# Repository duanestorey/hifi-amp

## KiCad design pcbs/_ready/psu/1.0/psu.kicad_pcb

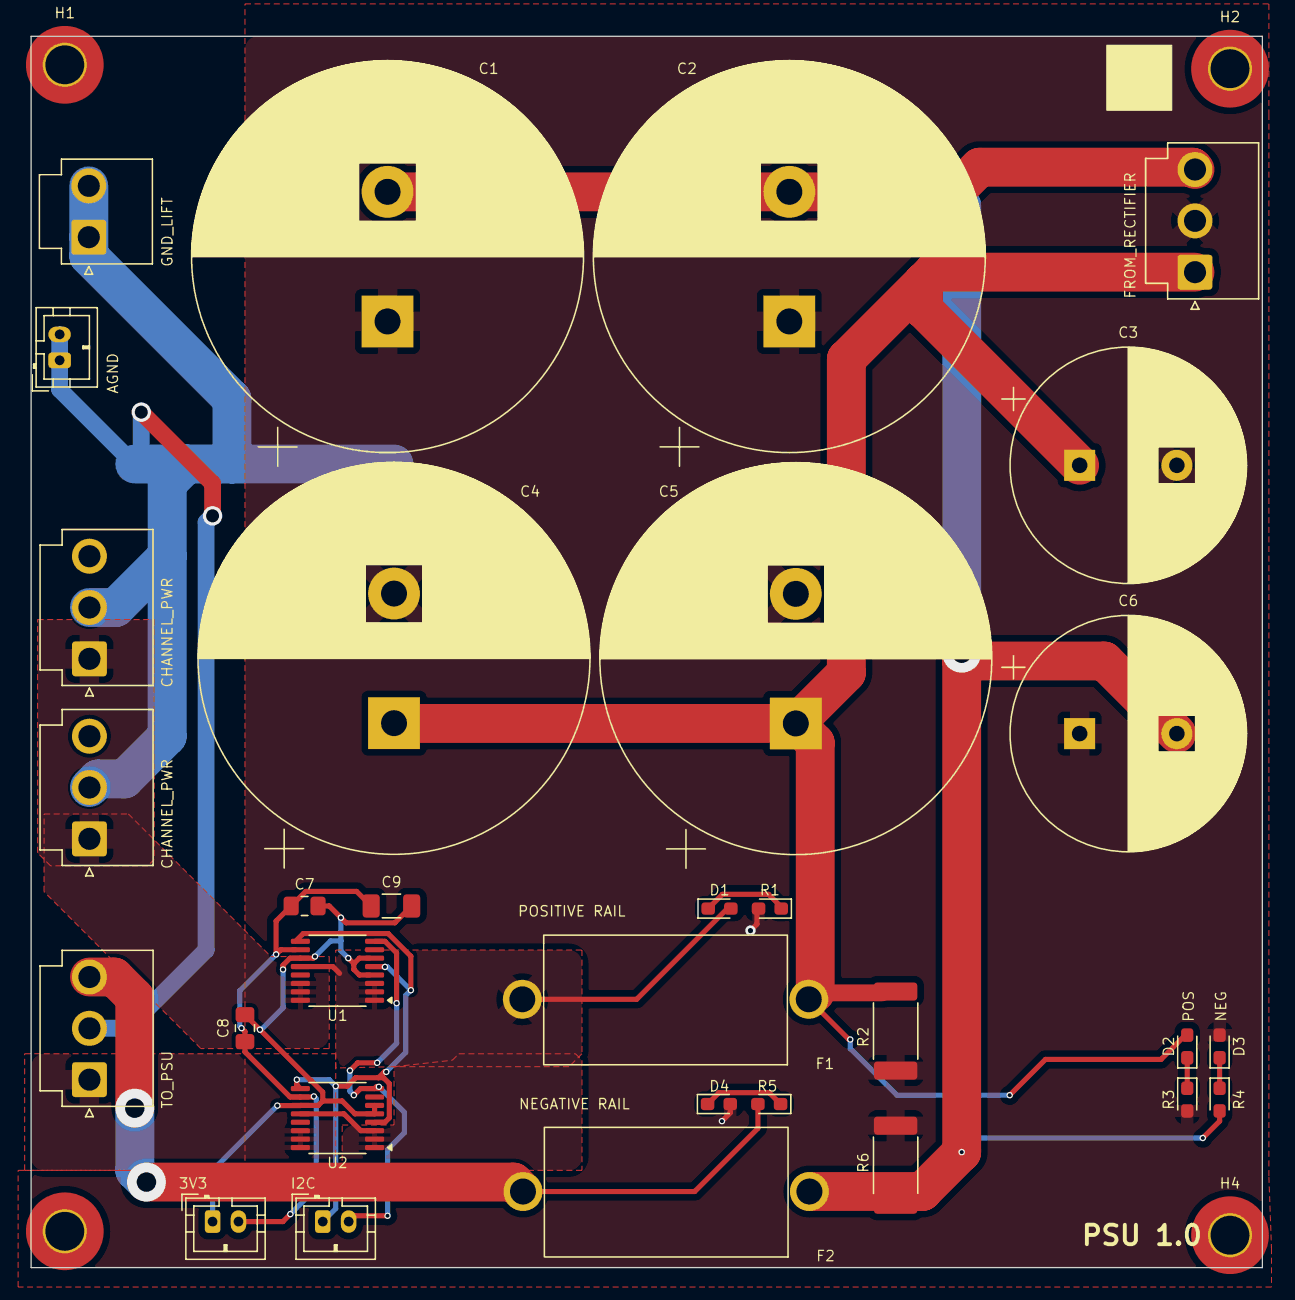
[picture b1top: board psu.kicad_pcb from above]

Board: 2 copper layers, 95.0 x 95.0 mm, 35 parts (0 on the bottom side), 15 nets.

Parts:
C1, C2, C4, C5: 15000U; CP_Radial_D30.0mm_P10.00mm_SnapIn
C3, C6: 3300u 50V; CP_Radial_D18.0mm_P7.50mm
C7, C8: 0.1u; C_0805_2012Metric_Pad1.18x1.45mm_HandSolder
C9: 10u; C_1206_3216Metric_Pad1.33x1.80mm_HandSolder
D1, D2: YELLOW; LED_0603_1608Metric_Pad1.05x0.95mm_HandSolder
D3, D4: BLUE; LED_0603_1608Metric_Pad1.05x0.95mm_HandSolder
F1, F2: Fuse_Small; Aliexpress Fuse 5x20
H1, H2, H3, H4: MountingHole; MountingHole_3mm_Pad_TopOnly
J1: Conn_01x02_Male; JST_VH_B2P-VH-B_1x02_P3.96mm_Vertical
J2, J4, J5, J6: Conn_01x03_Male; JST_VH_B3P-VH_1x03_P3.96mm_Vertical
J3, J7: Conn_01x02_Pin; JST_PH_B2B-PH-K_1x02_P2.00mm_Vertical
J8: Conn_01x02_Male; JST_PH_B2B-PH-K_1x02_P2.00mm_Vertical
R1, R3, R4, R5: 16K; LED_0603_1608Metric_Pad1.05x0.95mm_HandSolder
R2, R6: 1.5K 2W; R_2512_6332Metric_Pad1.40x3.35mm_HandSolder
U1, U2: INA260; TSSOP-16_4.4x5mm_P0.65mm

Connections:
3V3: C7.1, C8.1, C9.1, J7.2, U1.10 (VS), U2.10 (VS)
GND: C7.2, C8.2, C9.2, J7.1, U1.4 (A1), U1.6 (GND), U1.11 (GND), U2.5 (A0), U2.6 (GND), U2.11 (GND)
unnamed: D1.1 (K), R1.1
unnamed: D2.1 (K), R3.1
unnamed: D3.1 (K), R4.1
unnamed: D4.1 (K), R5.1
PGND: C1.1, C2.1, C3.2, C4.2, C5.2, C6.1, D3.2 (A), D4.2 (A), J1.1, J1.2, J2.2, J3.1, J3.2, J4.2, J5.2, J6.2, R1.2, R2.2, R3.2, R6.1
SCL: J8.1, U1.5 (A0), U1.9 (SCL), U2.4 (A1), U2.9 (SCL)
SDA: J8.2, U1.8 (SDA), U2.8 (SDA)
VM1: C1.2, C2.2, C6.2, F2.1, J2.3, R4.2, R6.2
VNOUT: F2.2, J4.3, J5.3, J6.3, R5.2
VP1: C3.1, C4.1, C5.1, D2.2 (A), F1.1, J2.1, R2.1
VPOUT: D1.2 (A), F1.2, U1.1 (IN+), U1.2 (IN+), U1.3 (IN+), U1.12 (VBUS), U2.1 (IN+), U2.2 (IN+), U2.3 (IN+), U2.12 (VBUS)
VPOUT_CHAN: J4.1, J5.1, U1.14 (IN-), U1.15 (IN-), U1.16 (IN-)
VPOUT_PSU: J6.1, U2.14 (IN-), U2.15 (IN-), U2.16 (IN-)

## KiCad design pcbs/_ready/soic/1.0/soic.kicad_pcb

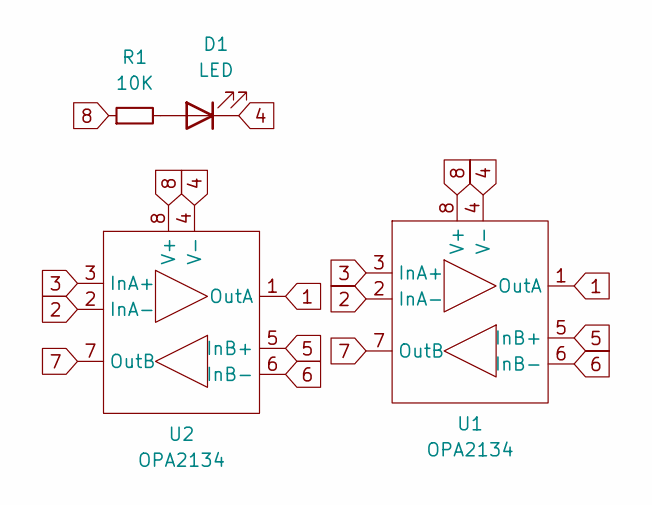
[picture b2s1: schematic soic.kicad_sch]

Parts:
D1: LED; LED_0603_1608Metric
R1: 10K; R_0603_1608Metric
U1: OPA2134; DIP-8_W7.62mm_Socket
U2: OPA2134; SOIC-8_3.9x4.9mm_P1.27mm

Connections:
1: U1.1 (OutA), U2.1 (OutA)
2: U1.2 (InA-), U2.2 (InA-)
3: U1.3 (InA+), U2.3 (InA+)
4: D1.1 (K), U1.4 (V-), U2.4 (V-)
5: U1.5 (InB+), U2.5 (InB+)
6: U1.6 (InB-), U2.6 (InB-)
7: U1.7 (OutB), U2.7 (OutB)
8: R1.1, U1.8 (V+), U2.8 (V+)
unnamed: D1.2 (A), R1.2

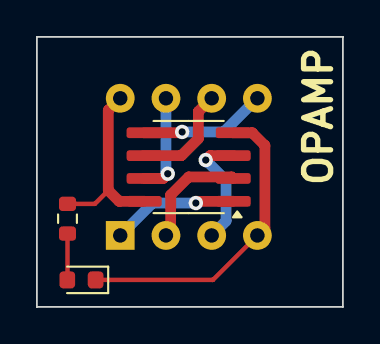
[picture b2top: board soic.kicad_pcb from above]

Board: 2 copper layers, 17.0 x 15.0 mm, 4 parts (0 on the bottom side), 9 nets.

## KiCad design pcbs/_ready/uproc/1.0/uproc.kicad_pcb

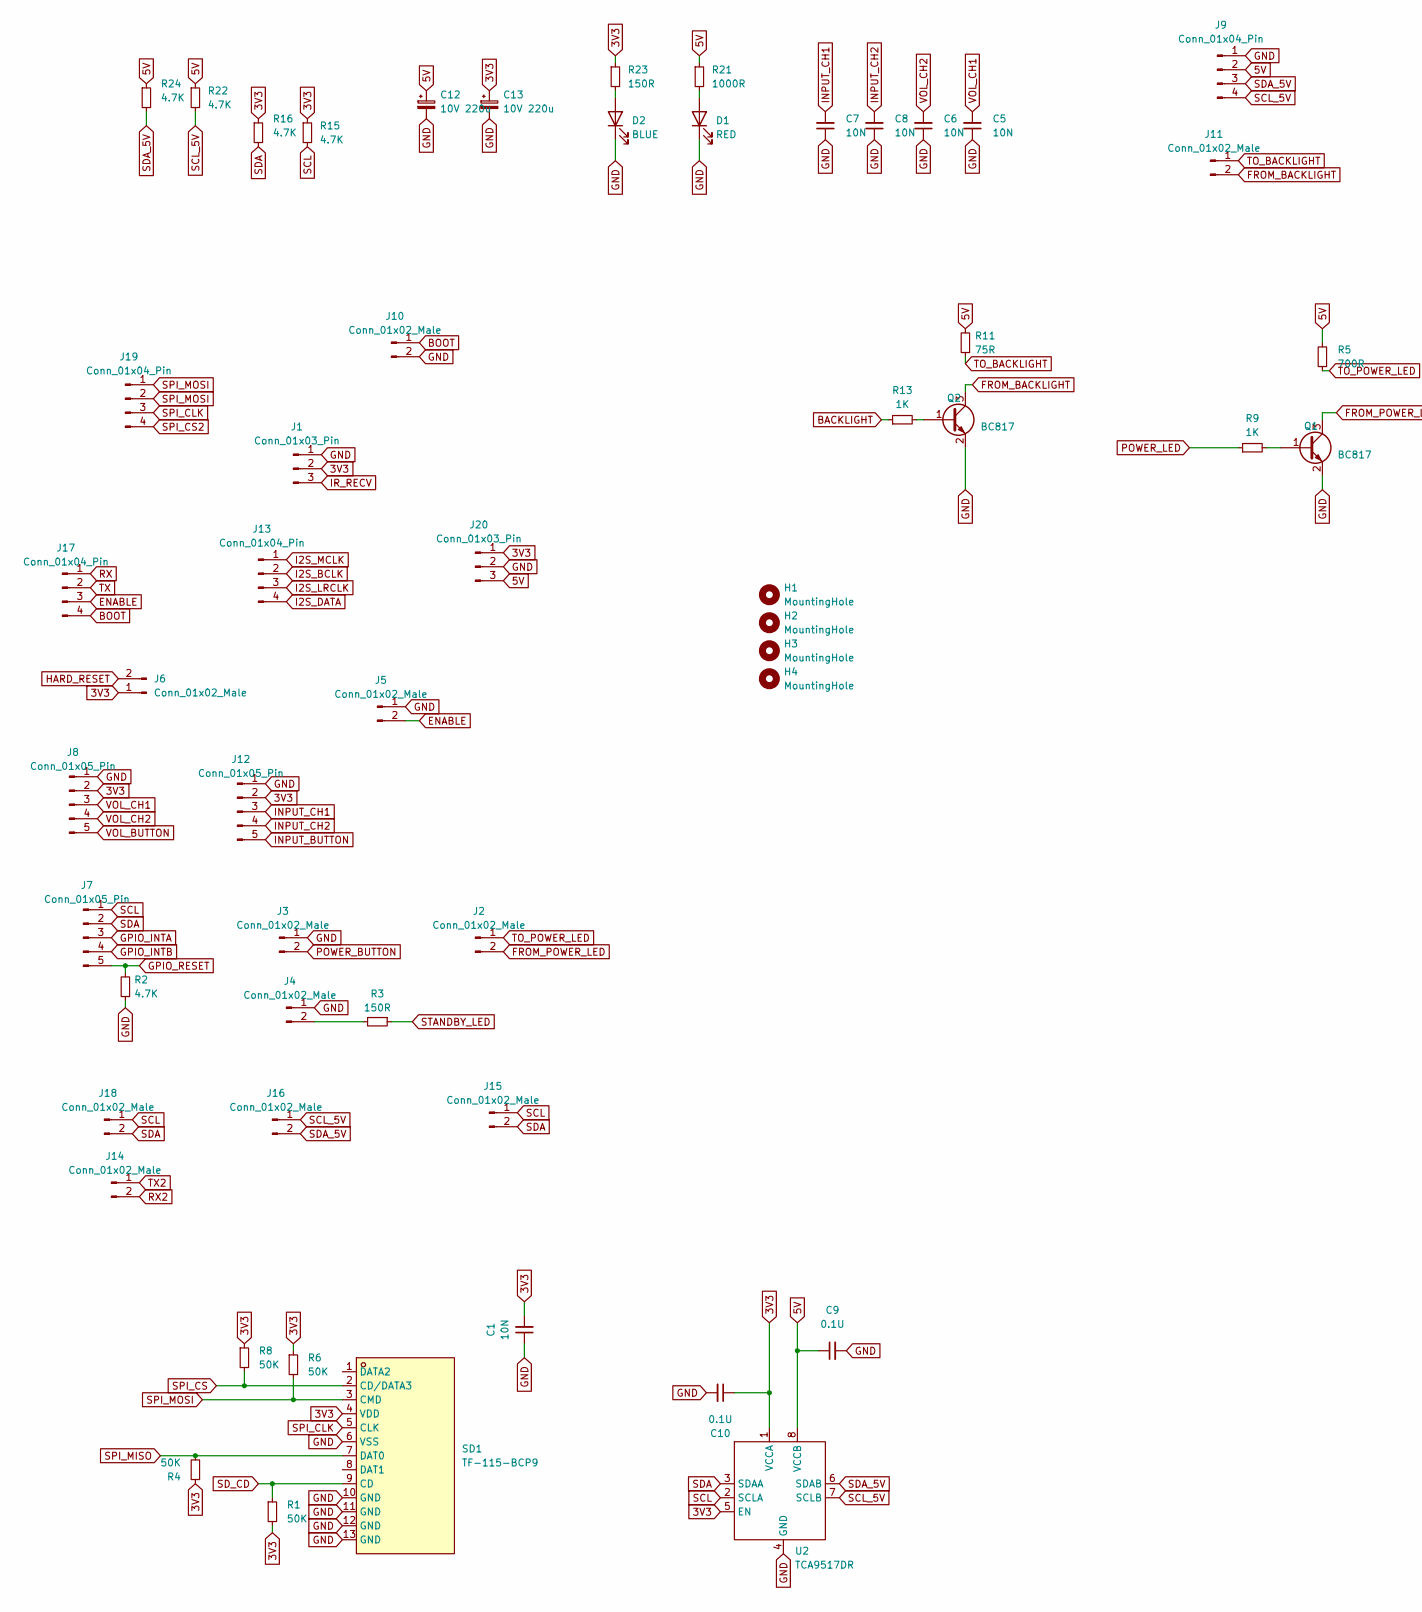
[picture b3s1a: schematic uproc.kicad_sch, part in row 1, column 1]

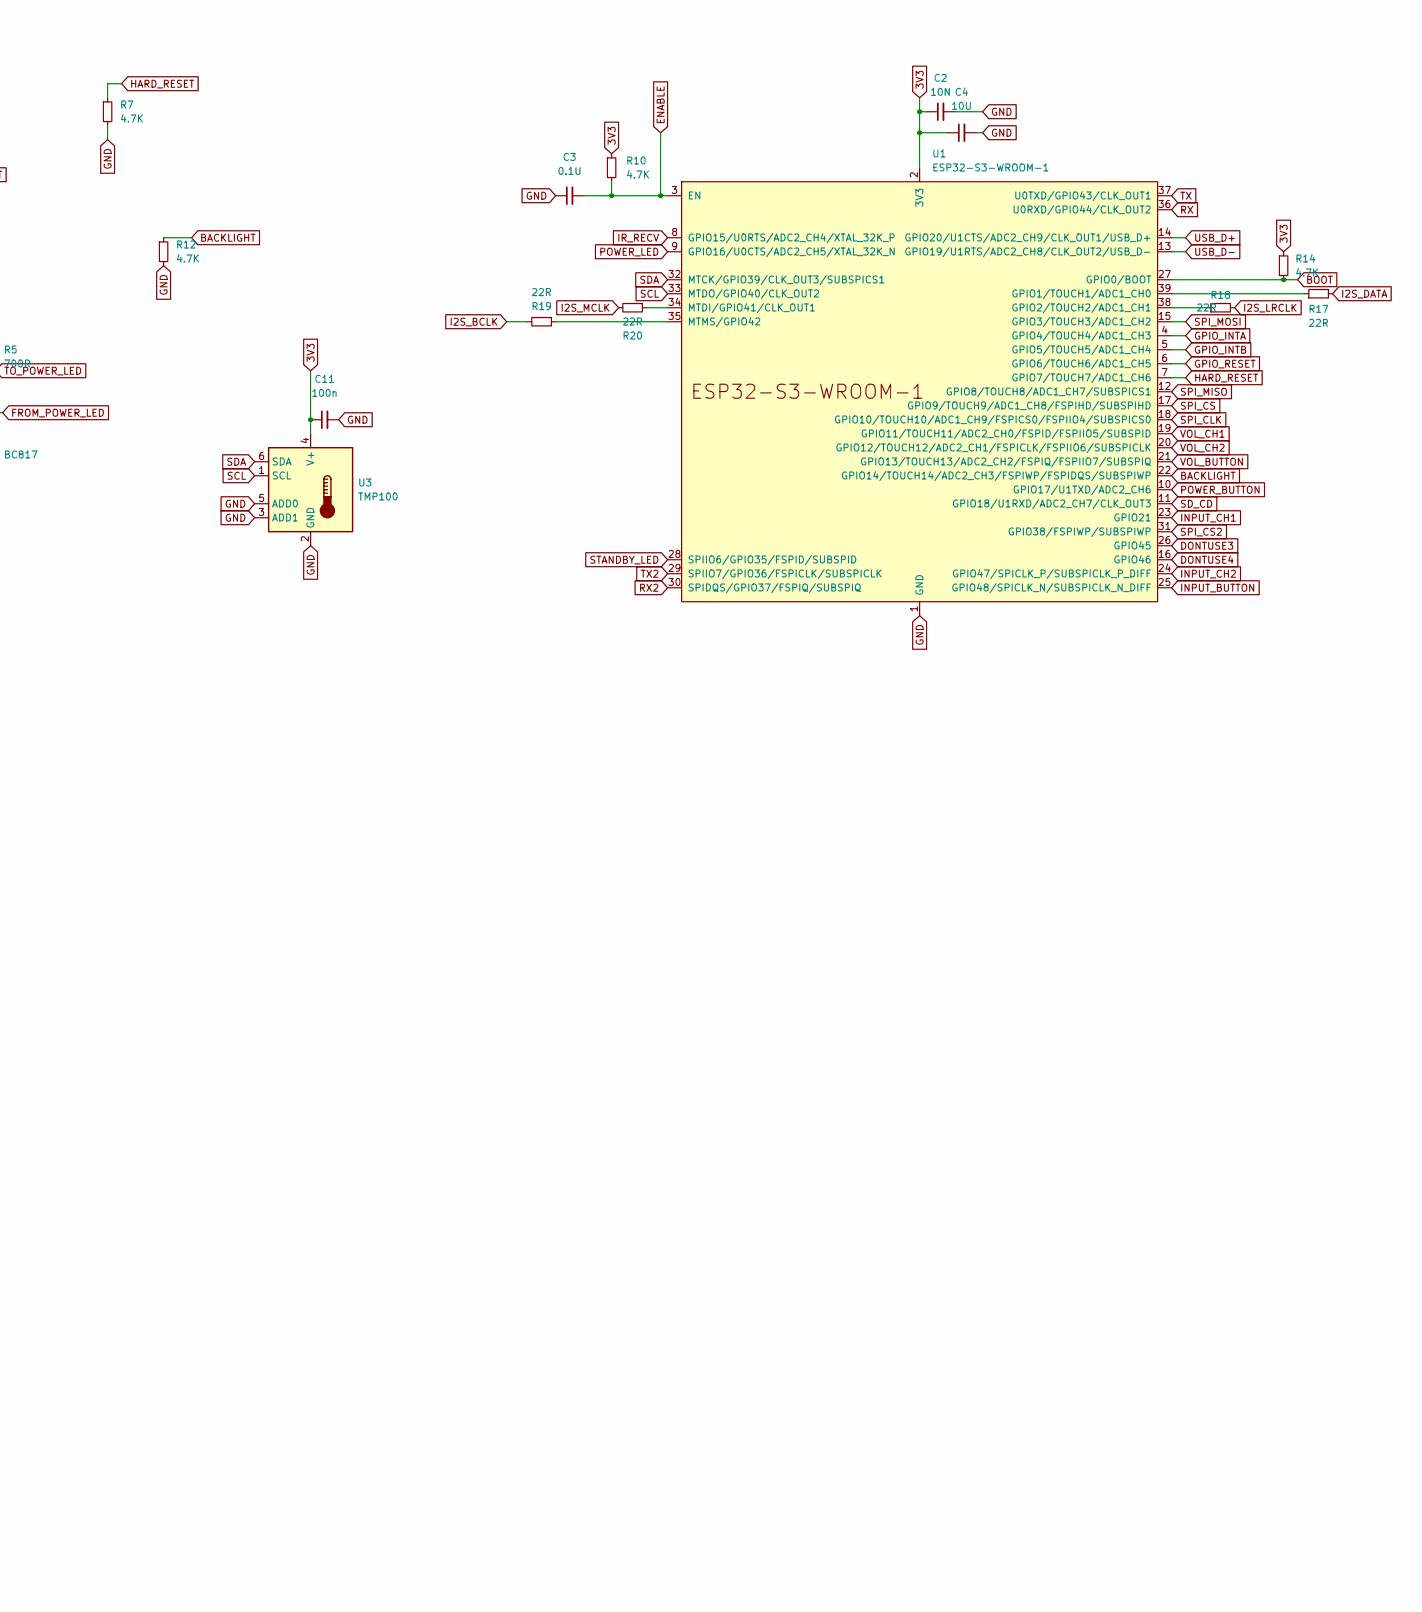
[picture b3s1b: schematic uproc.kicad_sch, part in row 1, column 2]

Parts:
C1, C2: 10N; C_0805_2012Metric_Pad1.18x1.45mm_HandSolder
C3, C9, C10: 0.1U; C_0805_2012Metric_Pad1.18x1.45mm_HandSolder
C4: 10U; C_1206_3216Metric_Pad1.33x1.80mm_HandSolder
C5, C6, C7, C8: 10N; C_0603_1608Metric_Pad1.08x0.95mm_HandSolder
C11: 100n; C_0805_2012Metric_Pad1.18x1.45mm_HandSolder
C12, C13: 10V 220u; CP_Radial_D6.3mm_P2.50mm
D1: RED; LED_0603_1608Metric; LCSC XL-1608UBC-04
D2: BLUE; LED_0603_1608Metric; LCSC NCD0603R1
H1, H2, H3, H4: MountingHole; MountingHole_3.2mm_M3_DIN965_Pad_TopOnly
J1, J20: Conn_01x03_Pin; JST_PH_B3B-PH-K_1x03_P2.00mm_Vertical
J2, J3, J4, J5, J11, J14, J15, J16, J18: Conn_01x02_Male; JST_PH_B2B-PH-K_1x02_P2.00mm_Vertical
J6, J10: Conn_01x02_Male; PinHeader_1x02_P2.54mm_Vertical
J7, J8, J12: Conn_01x05_Pin; JST_PH_B5B-PH-K_1x05_P2.00mm_Vertical
J9, J13, J17, J19: Conn_01x04_Pin; JST_PH_B4B-PH-K_1x04_P2.00mm_Vertical
Q1, Q2: BC817; TSOT-23; Mouser 637-BC817K-40
R1, R4, R6, R8: 50K; R_0603_1608Metric_Pad0.98x0.95mm_HandSolder
R2, R7, R10, R12, R14, R15, R16, R22, R24: 4.7K; R_0603_1608Metric_Pad0.98x0.95mm_HandSolder
R3, R23: 150R; R_0603_1608Metric_Pad0.98x0.95mm_HandSolder
R5: 700R; R_0603_1608Metric_Pad0.98x0.95mm_HandSolder
R9, R13: 1K; R_0603_1608Metric_Pad0.98x0.95mm_HandSolder
R11: 75R; R_0603_1608Metric_Pad0.98x0.95mm_HandSolder
R17, R18, R19, R20: 22R; R_0603_1608Metric; Mouser 603-RT0805FRE0722RL
R21: 1000R; R_0603_1608Metric_Pad0.98x0.95mm_HandSolder
SD1: TF-115-BCP9; TF-SMD_TF-115-BCP9; LCSC Part C720505
U1: ESP32-S3-WROOM-1
U2: TCA9517DR; SOIC-8_3.9x4.9mm_P1.27mm; Mouser 595-TCA9517DR
U3: TMP100; SOT-23-6

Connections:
3V3: C1.2, C2.1, C4.1, C10.1, C11.1, C13.1, J1.2, J6.1, J8.2, J12.2, J20.1, R1.2, R4.1, R6.1, R8.1, R10.1, R14.1, R15.1, R16.1, R23.1, SD1.4 (VDD), U1.2 (3V3), U2.1 (VCCA), U2.5 (EN), U3.4 (V+)
5V: C9.1, C12.1, J9.2, J20.3, R5.2, R11.2, R21.1, R22.1, R24.1, U2.8 (VCCB)
BACKLIGHT: R12.1, R13.1, U1.22 (GPIO14/TOUCH14/ADC2_CH3/FSPIWP/FSPIDQS/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)
BOOT: J10.1, J17.4, R14.2, U1.27 (GPIO0/BOOT)
DONTUSE3: U1.26 (GPIO45)
DONTUSE4: U1.16 (GPIO46)
ENABLE: C3.2, J5.2, J17.3, R10.2, U1.3 (EN)
FROM_BACKLIGHT: J11.2, Q2.3 (C)
FROM_POWER_LED: J2.2, Q1.3 (C)
GND: C1.1, C2.2, C3.1, C4.2, C5.1, C6.1, C7.1, C8.1, C9.2, C10.2, C11.2, C12.2, C13.2, D1.1 (K), D2.1 (K), J1.1, J3.1, J4.1, J5.1, J8.1, J9.1, J10.2, J12.1, J20.2, Q1.2 (E), Q2.2 (E), R2.1, R7.2, R12.2, SD1.6 (VSS), SD1.10 (GND), SD1.11 (GND), SD1.12 (GND), SD1.13 (GND), U1.1 (GND), U1.40 (GND), U1.41 (GND), U2.4 (GND), U3.2 (GND), U3.3 (ADD1), U3.5 (ADD0)
GPIO_INTA: J7.3, U1.4 (GPIO4/TOUCH4/ADC1_CH3)
GPIO_INTB: J7.4, U1.5 (GPIO5/TOUCH5/ADC1_CH4)
GPIO_RESET: J7.5, R2.2, U1.6 (GPIO6/TOUCH6/ADC1_CH5)
HARD_RESET: J6.2, R7.1, U1.7 (GPIO7/TOUCH7/ADC1_CH6)
I2S_BCLK: J13.2, R19.2
I2S_DATA: J13.4, R17.2
I2S_LRCLK: J13.3, R18.2
I2S_MCLK: J13.1, R20.2
INPUT_BUTTON: J12.5, U1.25 (GPIO48/SPICLK_N/SUBSPICLK_N_DIFF)
INPUT_CH1: C7.2, J12.3, U1.23 (GPIO21)
INPUT_CH2: C8.2, J12.4, U1.24 (GPIO47/SPICLK_P/SUBSPICLK_P_DIFF)
IR_RECV: J1.3, U1.8 (GPIO15/U0RTS/ADC2_CH4/XTAL_32K_P)
unnamed: D1.2 (A), R21.2
unnamed: D2.2 (A), R23.2
unnamed: J4.2, R3.2
unnamed: Q1.1 (B), R9.2
unnamed: Q2.1 (B), R13.2
unnamed: R17.1, U1.39 (GPIO1/TOUCH1/ADC1_CH0)
unnamed: R18.1, U1.38 (GPIO2/TOUCH2/ADC1_CH1)
unnamed: R20.1, U1.34 (MTDI/GPIO41/CLK_OUT1)
unnamed: R19.1, U1.35 (MTMS/GPIO42)
POWER_BUTTON: J3.2, U1.10 (GPIO17/U1TXD/ADC2_CH6)
POWER_LED: R9.1, U1.9 (GPIO16/U0CTS/ADC2_CH5/XTAL_32K_N)
RX: J17.1, U1.36 (U0RXD/GPIO44/CLK_OUT2)
RX2: J14.2, U1.30 (SPIDQS/GPIO37/FSPIQ/SUBSPIQ)
SCL: J7.1, J15.1, J18.1, R15.2, U1.33 (MTDO/GPIO40/CLK_OUT2), U2.2 (SCLA), U3.1 (SCL)
SCL_5V: J9.4, J16.1, R22.2, U2.7 (SCLB)
SDA: J7.2, J15.2, J18.2, R16.2, U1.32 (MTCK/GPIO39/CLK_OUT3/SUBSPICS1), U2.3 (SDAA), U3.6 (SDA)
SDA_5V: J9.3, J16.2, R24.2, U2.6 (SDAB)
SD_CD: R1.1, SD1.9 (CD), U1.11 (GPIO18/U1RXD/ADC2_CH7/CLK_OUT3)
SPI_CLK: J19.3, SD1.5 (CLK), U1.18 (GPIO10/TOUCH10/ADC1_CH9/FSPICS0/FSPIIO4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)
SPI_CS: R8.2, SD1.2 (CD/DATA3), U1.17 (GPIO9/TOUCH9/ADC1_CH8/FSPIHD/SUBSPIHD)
SPI_CS2: J19.4, U1.31 (GPIO38/FSPIWP/SUBSPIWP)
SPI_MISO: R4.2, SD1.7 (DAT0), U1.12 (GPIO8/TOUCH8/ADC1_CH7/SUBSPICS1)
SPI_MOSI: J19.1, J19.2, R6.2, SD1.3 (CMD), U1.15 (GPIO3/TOUCH3/ADC1_CH2)
STANDBY_LED: R3.1, U1.28 (SPIIO6/GPIO35/FSPID/SUBSPID)
TO_BACKLIGHT: J11.1, R11.1
TO_POWER_LED: J2.1, R5.1
TX: J17.2, U1.37 (U0TXD/GPIO43/CLK_OUT1)
TX2: J14.1, U1.29 (SPIIO7/GPIO36/FSPICLK/SUBSPICLK)
USB_D+: U1.14 (GPIO20/U1CTS/ADC2_CH9/CLK_OUT1/USB_D+)
USB_D-: U1.13 (GPIO19/U1RTS/ADC2_CH8/CLK_OUT2/USB_D-)
VOL_BUTTON: J8.5, U1.21 (GPIO13/TOUCH13/ADC2_CH2/FSPIQ/FSPIIO7/S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)
VOL_CH1: C5.2, J8.3, U1.19 (GPIO11/TOUCH11/ADC2_CH0/FSPID/FSPIIO5/S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)
VOL_CH2: C6.2, J8.4, U1.20 (GPIO12/TOUCH12/ADC2_CH1/FSPICLK/FSPIIO6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)

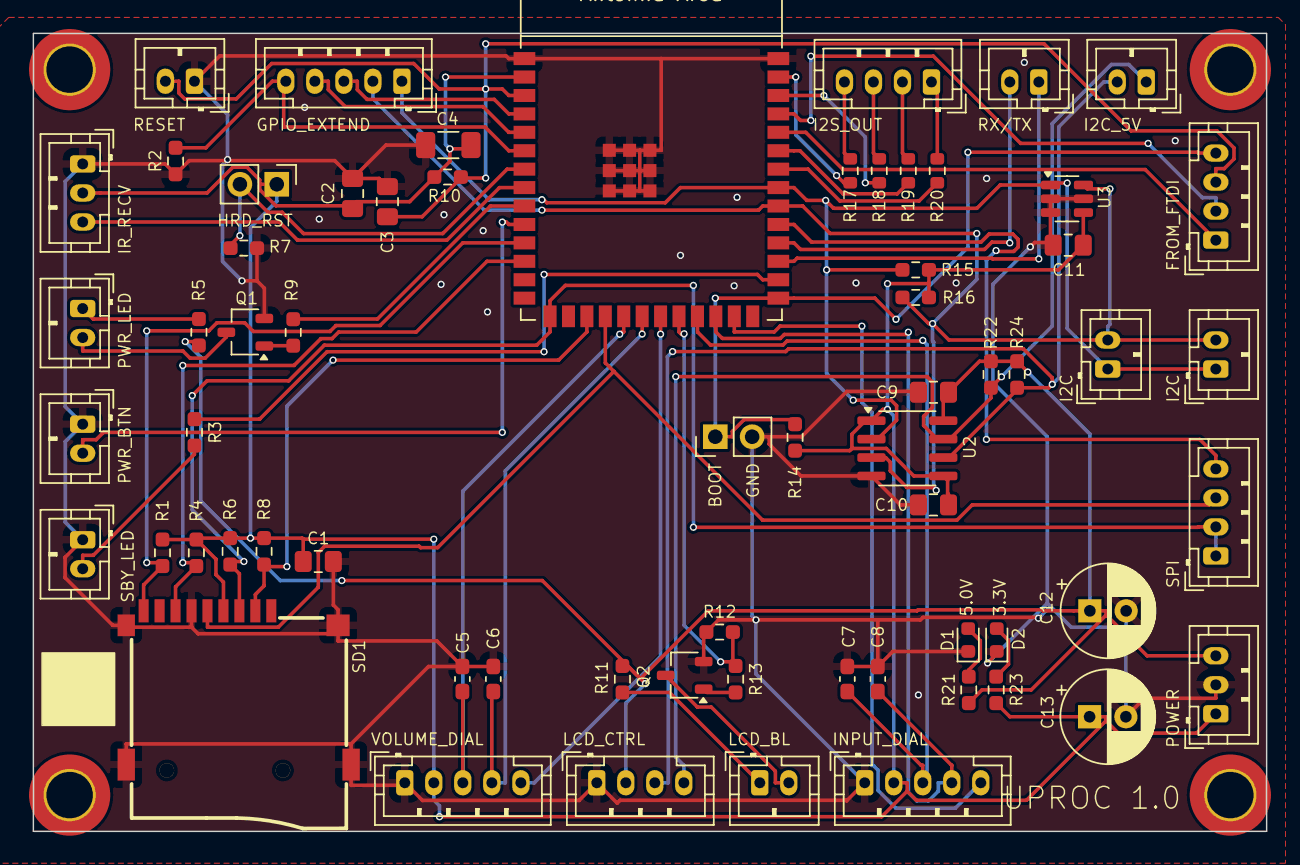
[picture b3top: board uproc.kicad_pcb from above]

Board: 2 copper layers, 85.0 x 55.0 mm, 69 parts (0 on the bottom side), 51 nets.

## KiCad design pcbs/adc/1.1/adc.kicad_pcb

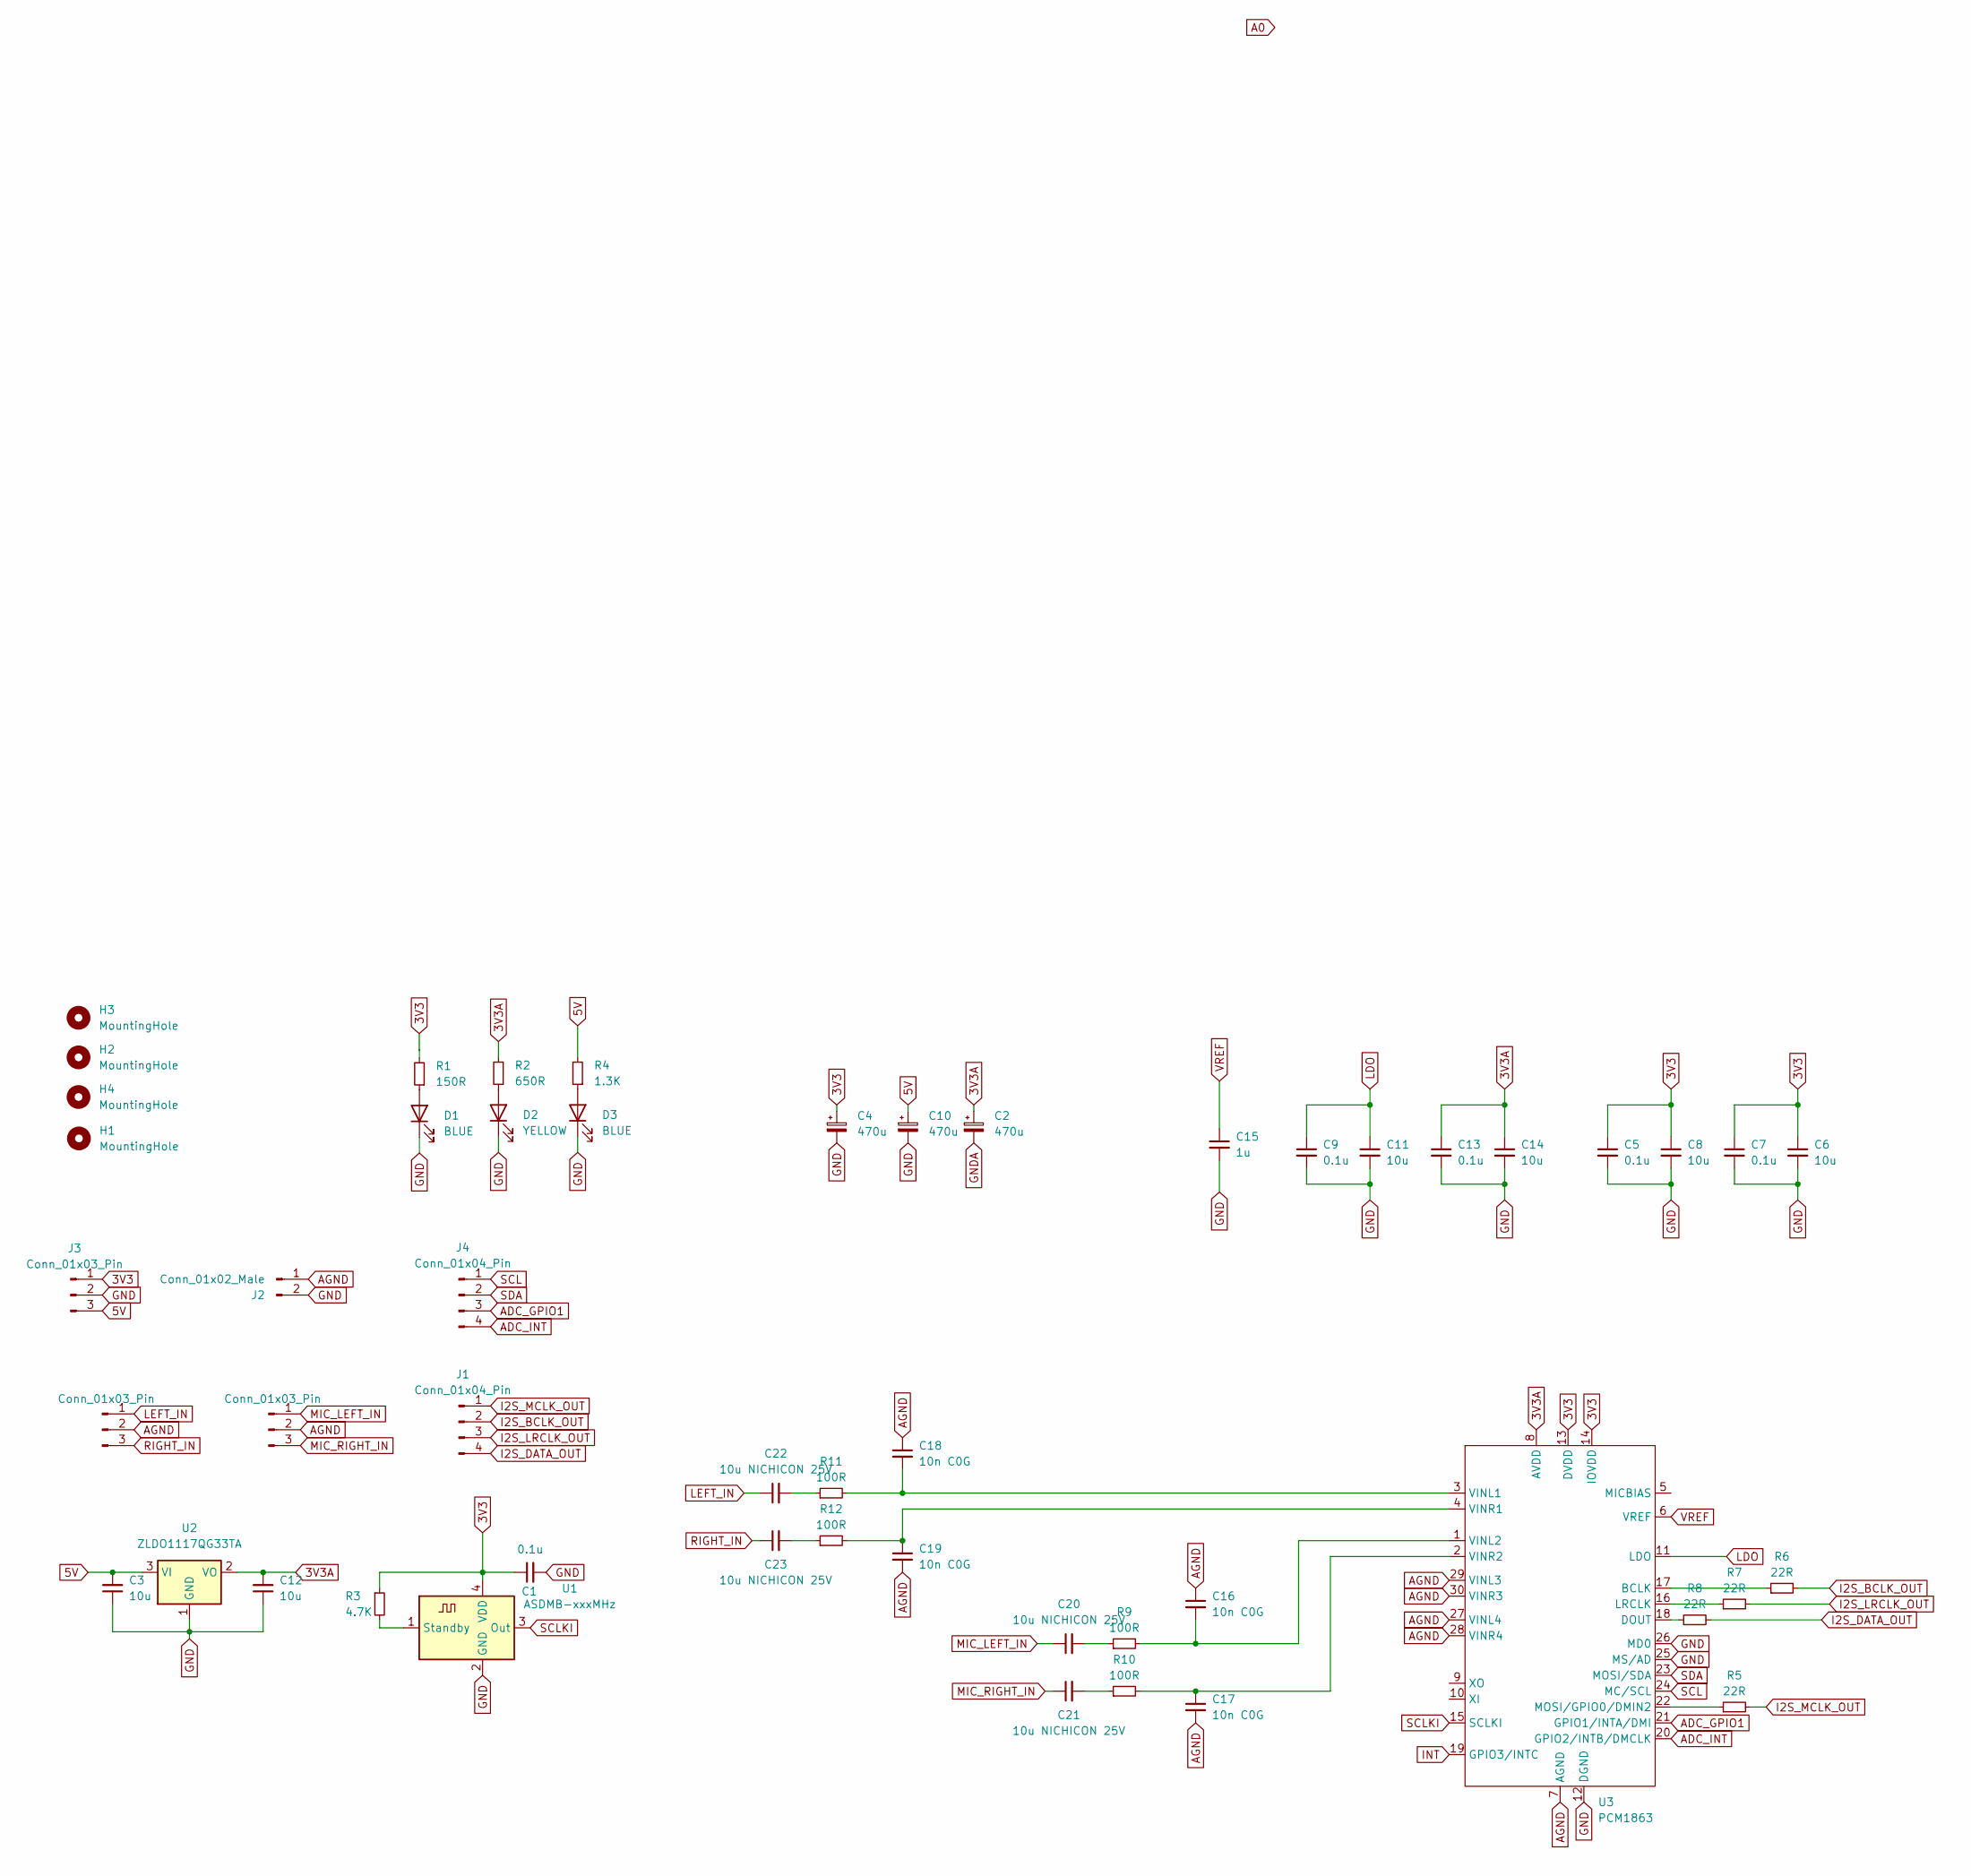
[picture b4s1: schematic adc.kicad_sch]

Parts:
C1: 0.1u; C_0805_2012Metric_Pad1.18x1.45mm_HandSolder; Mouser 791-0805N103G250CT
C2, C4, C10: 470u; CP_Radial_D6.3mm_P2.50mm
C3, C6, C8, C11, C12, C14: 10u; C_1206_3216Metric_Pad1.33x1.80mm_HandSolder
C5, C7, C9, C13: 0.1u; C_0805_2012Metric_Pad1.18x1.45mm_HandSolder
C15: 1u; C_1206_3216Metric_Pad1.33x1.80mm_HandSolder
C16, C17, C18, C19: 10n C0G; C_0805_2012Metric_Pad1.18x1.45mm_HandSolder; Mouser 791-0805N103G250CT
C20, C21, C22, C23: 10u NICHICON 25V; CP_Radial_D5.0mm_P2.00mm
D1, D3: BLUE; LED_0603_1608Metric
D2: YELLOW; LED_0603_1608Metric
H1, H2, H3, H4: MountingHole; MountingHole_3.2mm_M3_DIN965_Pad_TopOnly
J1, J4: Conn_01x04_Pin; JST_PH_B4B-PH-K_1x04_P2.00mm_Vertical
J2: Conn_01x02_Male; PinHeader_1x02_P2.54mm_Vertical
J3, J5, J6: Conn_01x03_Pin; JST_PH_B3B-PH-K_1x03_P2.00mm_Vertical
R1: 150R; R_0603_1608Metric_Pad0.98x0.95mm_HandSolder
R2: 650R; R_0603_1608Metric_Pad0.98x0.95mm_HandSolder
R3: 4.7K; R_0603_1608Metric_Pad0.98x0.95mm_HandSolder; Mouser 603-RT0805FRE0722RL
R4: 1.3K; R_0603_1608Metric_Pad0.98x0.95mm_HandSolder
R5, R6, R7, R8: 22R; R_0805_2012Metric_Pad1.20x1.40mm_HandSolder; Mouser 603-RT0805FRE0722RL
R9, R10, R11, R12: 100R; R_0805_2012Metric_Pad1.20x1.40mm_HandSolder; Mouser 603-RT0805FRE13100RL
U1: ASDMB-xxxMHz; Oscillator_SMD_Abracon_ASE-4Pin_3.2x2.5mm; Mouser 346-3225Z24.5760C1KX
U2: ZLDO1117QG33TA; SOT-223-3_TabPin2
U3: PCM1863; TSSOP-30_4.4x7.8mm_P0.5mm; Mouser 595-PCM1863DBT

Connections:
3V3: C1.1, C4.1, C5.1, C6.1, C7.1, C8.1, J3.1, R1.2, R3.1, U1.4 (VDD), U3.13 (DVDD), U3.14 (IOVDD)
3V3A: C2.1, C12.2, C13.1, C14.1, R2.2, U2.2 (VO), U3.8 (AVDD)
5V: C3.2, C10.1, J3.3, R4.2, U2.3 (VI)
ADC_GPIO1: J4.3, U3.21 (GPIO1/INTA/DMI)
ADC_INT: J4.4, U3.20 (GPIO2/INTB/DMCLK)
AGND: C16.1, C17.2, C18.1, C19.2, J2.1, J5.2, J6.2, U3.7 (AGND), U3.27 (VINL4), U3.28 (VINR4), U3.29 (VINL3), U3.30 (VINR3)
GND: C1.2, C3.1, C4.2, C5.2, C6.2, C7.2, C8.2, C9.2, C10.2, C11.2, C12.1, C13.2, C14.2, C15.2, D1.1 (K), D2.1 (K), D3.1 (K), J2.2, J3.2, U1.2 (GND), U2.1 (GND), U3.12 (DGND), U3.25 (MS/AD), U3.26 (MD0)
GNDA: C2.2
I2S_BCLK_OUT: J1.2, R6.2
I2S_DATA_OUT: J1.4, R8.2
I2S_LRCLK_OUT: J1.3, R7.2
I2S_MCLK_OUT: J1.1, R5.2
INT: U3.19 (GPIO3/INTC)
LDO: C9.1, C11.1, U3.11 (LDO)
LEFT_IN: C22.1, J6.1
MIC_LEFT_IN: C20.1, J5.1
MIC_RIGHT_IN: C21.1, J5.3
unnamed: C20.2, R9.1
unnamed: C21.2, R10.1
unnamed: C22.2, R11.1
unnamed: C23.2, R12.1
unnamed: D1.2 (A), R1.1
unnamed: D2.2 (A), R2.1
unnamed: D3.2 (A), R4.1
unnamed: R3.2, U1.1 (Standby)
unnamed: R6.1, U3.17 (BCLK)
unnamed: R8.1, U3.18 (DOUT)
unnamed: R7.1, U3.16 (LRCLK)
unnamed: R5.1, U3.22 (MOSI/GPIO0/DMIN2)
unnamed: C18.2, R11.2, U3.3 (VINL1)
unnamed: C16.2, R9.2, U3.1 (VINL2)
unnamed: C19.1, R12.2, U3.4 (VINR1)
unnamed: C17.1, R10.2, U3.2 (VINR2)
RIGHT_IN: C23.1, J6.3
SCL: J4.1, U3.24 (MC/SCL)
SCLKI: U1.3 (Out), U3.15 (SCLKI)
SDA: J4.2, U3.23 (MOSI/SDA)
VREF: C15.1, U3.6 (VREF)

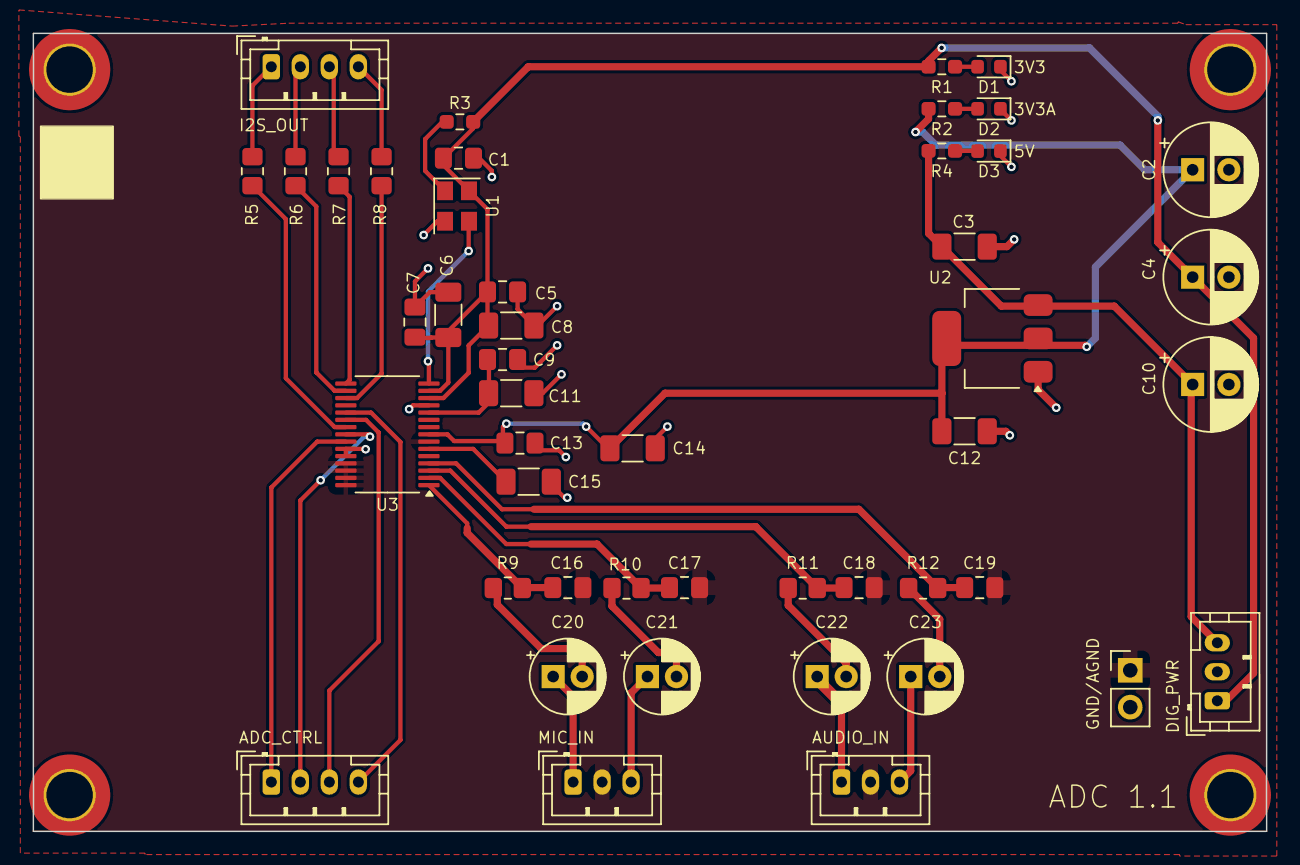
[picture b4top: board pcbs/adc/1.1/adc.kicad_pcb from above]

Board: 2 copper layers, 85.0 x 55.0 mm, 51 parts (0 on the bottom side), 36 nets.
